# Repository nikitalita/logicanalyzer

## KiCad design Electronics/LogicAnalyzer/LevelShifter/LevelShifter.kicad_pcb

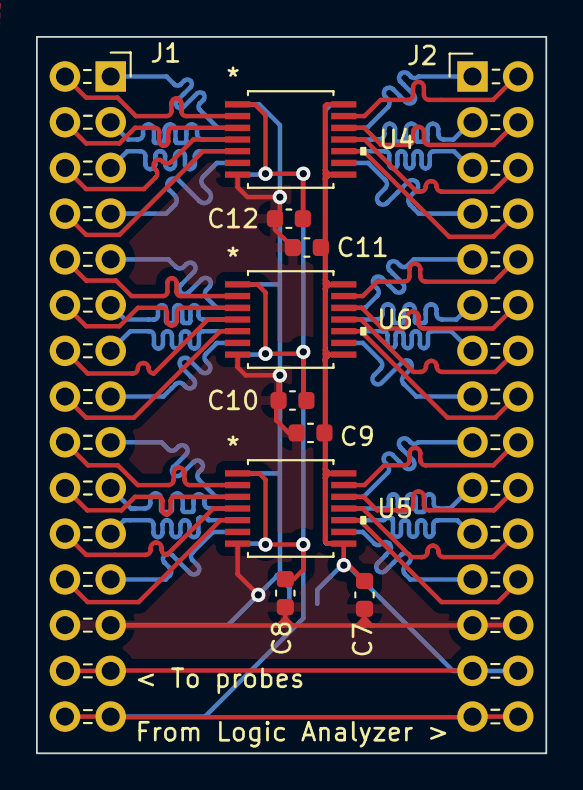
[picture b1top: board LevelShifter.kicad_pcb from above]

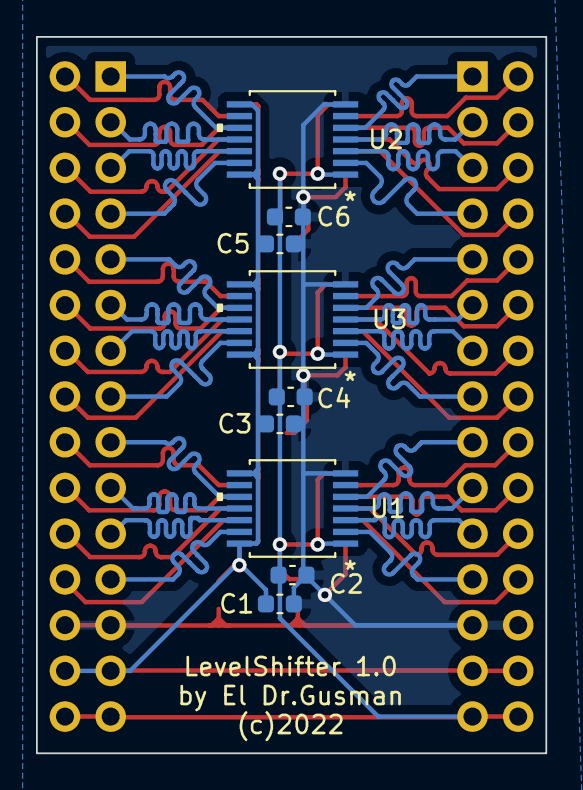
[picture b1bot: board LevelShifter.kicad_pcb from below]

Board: 2 copper layers, 28.3 x 39.8 mm, 20 parts (9 on the bottom side), 51 nets.

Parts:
C1, C2, C3, C4, C5, C6, C7, C8, C9, C10, C11, C12: C; C_0603_1608Metric
J1: Conn_02x15_Odd_Even; PinSocket_2x15_P2.54mm_Horizontal
J2: Conn_02x15_Odd_Even; PinHeader_2x15_P2.54mm_Horizontal
U1, U2, U3, U4, U5, U6: TXU0104PWR

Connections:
/3V3: C1.1, C3.1, C5.1, C7.1, C9.1, C11.1, J1.27, J1.28, J2.27, J2.28, U1.8 (OE), U1.14 (VCCB), U2.8 (OE), U2.14 (VCCB), U3.8 (OE), U3.14 (VCCB), U4.8 (OE), U4.14 (VCCB), U5.8 (OE), U5.14 (VCCB), U6.8 (OE), U6.14 (VCCB)
/5V: C2.2, C4.2, C6.2, C8.2, C10.2, C12.2, J1.29, J1.30, J2.29, J2.30, U1.1 (VCCA), U2.1 (VCCA), U3.1 (VCCA), U4.1 (VCCA), U5.1 (VCCA), U6.1 (VCCA)
/CHAN_0_IN: J1.1, U2.5 (A4)
/CHAN_0_OUT: J2.1, U2.10 (B4Y)
/CHAN_1_IN: J1.3, U2.4 (A3)
/CHAN_1_OUT: J2.3, U2.11 (B3Y)
/CHAN_2_IN: J1.5, U2.3 (A2)
/CHAN_2_OUT: J2.5, U2.12 (B2Y)
/CHAN_3_IN: J1.7, U2.2 (A1)
/CHAN_3_OUT: J2.7, U2.13 (B1Y)
/CHAN_4_IN: J1.9, U3.5 (A4)
/CHAN_4_OUT: J2.9, U3.10 (B4Y)
/CHAN_5_IN: J1.11, U3.4 (A3)
/CHAN_5_OUT: J2.11, U3.11 (B3Y)
/CHAN_6_IN: J1.13, U3.3 (A2)
/CHAN_6_OUT: J2.13, U3.12 (B2Y)
/CHAN_7_IN: J1.15, U3.2 (A1)
/CHAN_7_OUT: J2.15, U3.13 (B1Y)
/CHAN_8_IN: J1.17, U1.5 (A4)
/CHAN_8_OUT: J2.17, U1.10 (B4Y)
/CHAN_9_IN: J1.19, U1.4 (A3)
/CHAN_9_OUT: J2.19, U1.11 (B3Y)
/CHAN_10_IN: J1.21, U1.3 (A2)
/CHAN_10_OUT: J2.21, U1.12 (B2Y)
/CHAN_11_IN: J1.23, U1.2 (A1)
/CHAN_11_OUT: J2.23, U1.13 (B1Y)
/CHAN_12_IN: J1.24, U5.5 (A4)
/CHAN_12_OUT: J2.24, U5.10 (B4Y)
/CHAN_13_IN: J1.22, U5.4 (A3)
/CHAN_13_OUT: J2.22, U5.11 (B3Y)
/CHAN_14_IN: J1.20, U5.3 (A2)
/CHAN_14_OUT: J2.20, U5.12 (B2Y)
/CHAN_15_IN: J1.18, U5.2 (A1)
/CHAN_15_OUT: J2.18, U5.13 (B1Y)
/CHAN_16_IN: J1.16, U6.5 (A4)
/CHAN_16_OUT: J2.16, U6.10 (B4Y)
/CHAN_17_IN: J1.14, U6.4 (A3)
/CHAN_17_OUT: J2.14, U6.11 (B3Y)
/CHAN_18_IN: J1.12, U6.3 (A2)
/CHAN_18_OUT: J2.12, U6.12 (B2Y)
/CHAN_19_IN: J1.10, U6.2 (A1)
/CHAN_19_OUT: J2.10, U6.13 (B1Y)
/CHAN_20_IN: J1.8, U4.5 (A4)
/CHAN_20_OUT: J2.8, U4.10 (B4Y)
/CHAN_21_IN: J1.6, U4.4 (A3)
/CHAN_21_OUT: J2.6, U4.11 (B3Y)
/CHAN_22_IN: J1.4, U4.3 (A2)
/CHAN_22_OUT: J2.4, U4.12 (B2Y)
/CHAN_23_IN: J1.2, U4.2 (A1)
/CHAN_23_OUT: J2.2, U4.13 (B1Y)
/GND: C1.2, C2.1, C3.2, C4.1, C5.2, C6.1, C7.2, C8.1, C9.2, C10.1, C11.2, C12.1, J1.25, J1.26, J2.25, J2.26, U1.7 (GND), U2.7 (GND), U3.7 (GND), U4.7 (GND), U5.7 (GND), U6.7 (GND)

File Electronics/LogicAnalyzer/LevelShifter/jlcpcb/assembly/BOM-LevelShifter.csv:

Comment,Designator,Footprint,LCSC
C,"C1,C10,C11,C12,C2,C3,C4,C5,C6,C7,C8,C9",C_0603_1608Metric,C14663
Conn_02x15_Odd_Even,J1,PinSocket_2x15_P2.54mm_Horizontal,
TXU0104PWR,U6,TXU0104PWR,
TXU0104PWR,U5,TXU0104PWR,
Conn_02x15_Odd_Even,J2,PinHeader_2x15_P2.54mm_Horizontal,
TXU0104PWR,U4,TXU0104PWR,
TXU0104PWR,U2,TXU0104PWR,
TXU0104PWR,U1,TXU0104PWR,
TXU0104PWR,U3,TXU0104PWR,

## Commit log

2023-02-08 WIP Changes

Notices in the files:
Electronics/LogicAnalyzer/LevelShifter/LevelShifter.kicad_pcb:
(c)2022
parts and their libraries:
Copyright 2021 Accelerated Designs. All rights reserved.
